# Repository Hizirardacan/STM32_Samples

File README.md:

# STM32 Embedded Projects Collection

This repository contains a collection of embedded C projects developed for STM32-based development boards, primarily the **NUCLEO-F401RE** and **NUCLEO-F746ZG**. Each project demonstrates a specific peripheral or system-level feature using STM32 HAL libraries and CMSIS.

---

## 🔧 Projects Overview

### ✅ Project 1: LED Blinker with Timer Interrupt (STM32F401RE)

- **Board:** NUCLEO-F401RE  
- **Function:** Toggles onboard LED (PA5, LD2) every 0.5 seconds using TIM2 interrupt.  
- **Timer Settings:**  
  - Prescaler = 8399, Period = 5000 → 0.5s interval  
  - Clock: HSE = 8 MHz → PLL = 84 MHz SYSCLK  

---

### ✅ Project 2: ADC Voltage Averaging with Button-triggered UART Output (STM32F401RE)

- **Board:** NUCLEO-F401RE  
- **Functionality:**
  - Continuously reads analog voltage from ADC1 (PA0)
  - Maintains a circular buffer of 1024 readings
  - On blue button press:
    - Turns on LD2 (PA5)
    - Prints averaged voltage over USART2 (USB serial)
    - Turns off LED  
- **Clock Configuration:**  
  SYSCLK = 84 MHz (PLL), APB1 = 42 MHz, 12-bit ADC  

---

### ✅ Project 3: DAC Output Controlled by UART + ADC Monitoring (STM32F746ZG)

- **Board:** NUCLEO-F746ZG  
- **Features:**  
  - Receives 3-character float over UART3  
  - Outputs voltage via DAC Channel 1  
  - Reads back via ADC and sends measured value over UART  
  - LEDs indicate activity: Red (idle), Blue (active)  
- **Note:** Uses polling, not interrupts.  

---

### ✅ Project 4: Interrupt-based UART + DAC Output + ADC Monitoring + Button Interaction (STM32F746ZG)

- **Board:** NUCLEO-F746ZG  
- **Highlights:**
  - UART3 uses `HAL_UART_Receive_IT` for 3-byte float input  
  - DAC outputs the received voltage  
  - ADC1 continuously samples PA0  
  - Averages 1024 samples and stores as `avg`  
  - On button press, sends `avg` over UART  
  - LEDs indicate status: Blue (DAC update), Red (idle), Green (button press)  

---

### ✅ Project 5: UART-controlled DAC Generator with Start-End Delimiters (STM32F746ZG)

- **Board:** NUCLEO-F746ZG  
- **Functionality:**
  - UART input format: `*<float>*` (e.g., `*1.234*`)  
  - Characters are received one-by-one with interrupt  
  - Parsed float is converted to DAC output  
  - ADC monitors DAC output and stores average  
  - Button press sends average voltage over UART  
- **Use Case:** PC-controlled analog simulation, signal loopback, or testing  

---

### ✅ Project 6: Dual ADC Voltage Averaging and UART Transmission (STM32F401RE or Similar)

- **Board:** STM32F4 Series (e.g., NUCLEO-F401RE)  
- **Function:**  
  - Continuously samples 2 ADC channels  
  - Averages 1024 samples per channel  
  - Transmits both voltages via USART2 every 200 ms  
  - PA11 is driven HIGH at system startup  

---

## 🧰 Development Tools

- **IDE:** STM32CubeIDE  
- **HAL Drivers:** STM32Cube HAL (F4 and F7 series)  
- **UART Communication:** Serial via USB (115200 baud)  
- **ADC/DAC Resolution:** 12-bit  
- **Language:** C (C99)

---

## 📦 Folder Structure

```
/Project1_TimerBlink
/Project2_ADC_Button_UART
/Project3_UART_DAC_ADC_Polling
/Project4_UART_DAC_ADC_Interrupt
/Project5_UART_Delimited_DAC
/2ADC_VoltageDivConfig
```

Each folder contains the corresponding STM32CubeMX-generated project, `main.c`, and peripheral configurations.

---

## 📌 Notes

- All projects are tested on the actual hardware.
- For UART testing, use a serial terminal like PuTTY or Tera Term.
- Ensure the correct COM port and baud rate (115200) is selected.

---

## 📄 License

This repository is open-source and available under the [MIT License](LICENSE).

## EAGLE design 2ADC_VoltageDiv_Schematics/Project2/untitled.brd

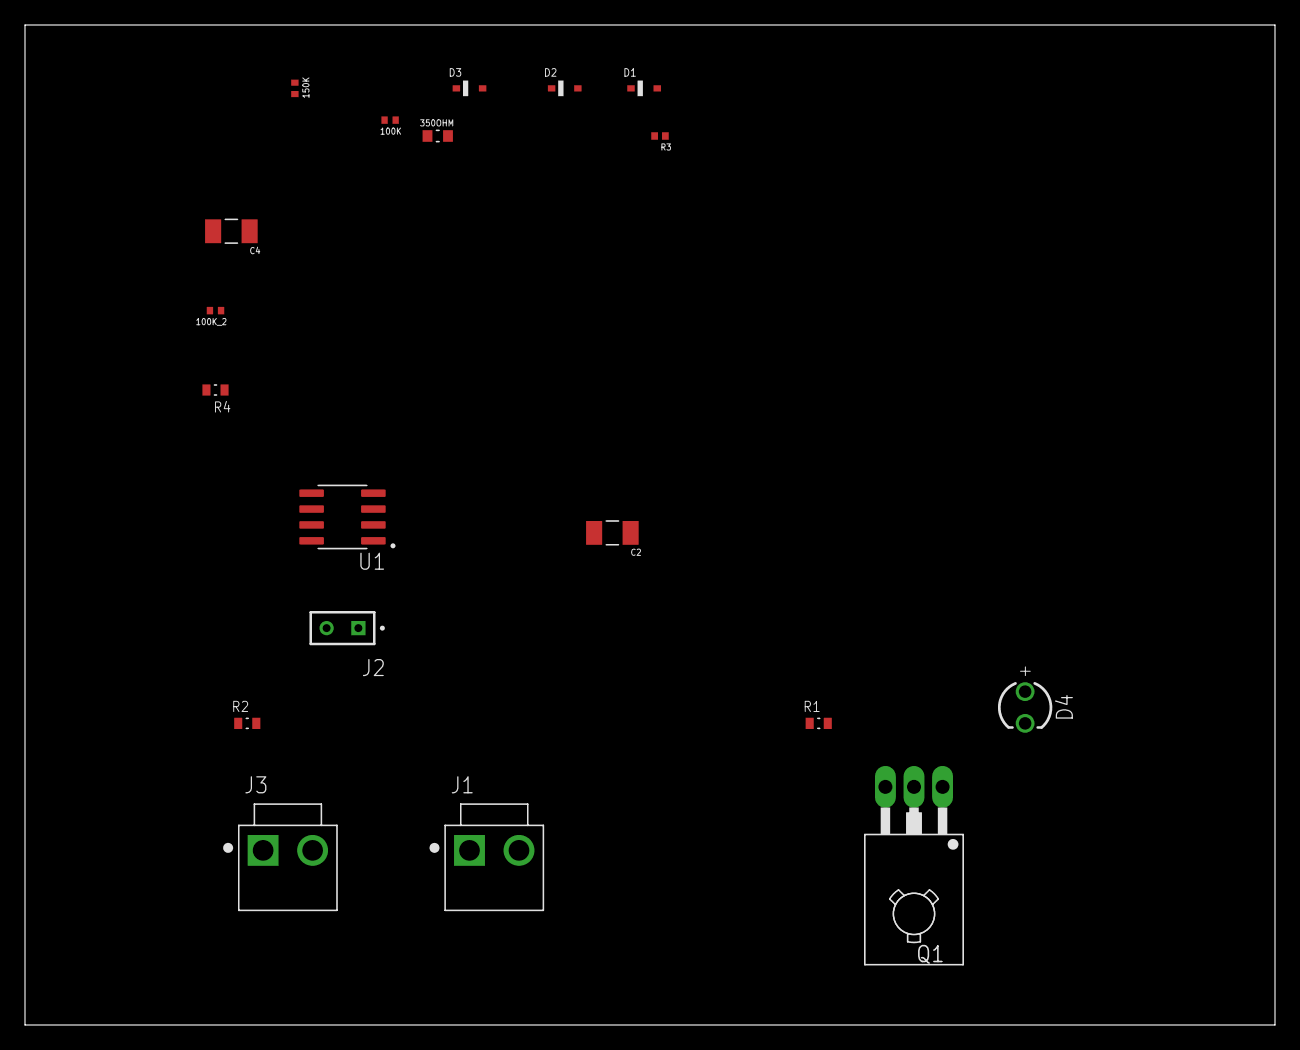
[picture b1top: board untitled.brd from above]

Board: 2 copper layers, 100.0 x 80.0 mm, 19 parts (0 on the bottom side), 14 nets, no tracks yet.

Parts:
100K, 100K_2: CRCW0402100KFKED; RESC1005X40N
150K: CPF0402B150KE1; RESC1005X35N
350OHM: RT0603DRE07352RL; RESC1608X55N
C2, C4: GRM31CD80J107MEA8L; CAPC3216X190N
D1, D2, D3: 1N4148WS-7-F; SOD2513X120N
D4: WL-TMRC_3MM_WITHOUTSTOPPER; WL-TMRC_3MM
J1, J3: 1-1123723-2; TE_1-1123723-2
J2: TS-102-G-A; SAMTEC_TS-102-G-A
Q1: BD139; TO126
R1, R2: ERA3AEB152V; RES_ERA3AEB152V
R3: RC0402FR-07649RL; RESC1005X40N
R4: ERA3AEB151V; RES_ERA3AEB151V
U1: LM358DR; SOIC127P599X175-8N

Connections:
3.3V: J3.2, R1.1
+5V: J3.1, R2.2, U1.8
ADC2: J2.02, U1.5, U1.7
GROUND: 150K.1, C2.1, C4.1, D3.C, J1.1, Q1.1, R3.1, R4.1, U1.4
unnamed: Q1.3, R1.2
unnamed: D2.C, D3.A
unnamed: 100K_2.1, 350OHM.2, D1.A, R3.2
unnamed: D1.C, D2.A
unnamed: 100K.2, 150K.2, C2.2, U1.2
unnamed: 100K_2.2, C4.2, R4.2, U1.6
unnamed: D4.1, R2.1
unnamed: D4.2, Q1.2
unnamed: J2.01, U1.1, U1.3
VIN: 100K.1, 350OHM.1, J1.2

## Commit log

2025-08-01 Sample Projects
2025-08-01 LTSPICE and EAGLE Schematics
2025-08-01 Project Explanations Added
2025-08-01 Update LICENSE
